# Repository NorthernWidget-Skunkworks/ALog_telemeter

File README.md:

# ALog_telemeter
ALog with a new core chip and telemetry

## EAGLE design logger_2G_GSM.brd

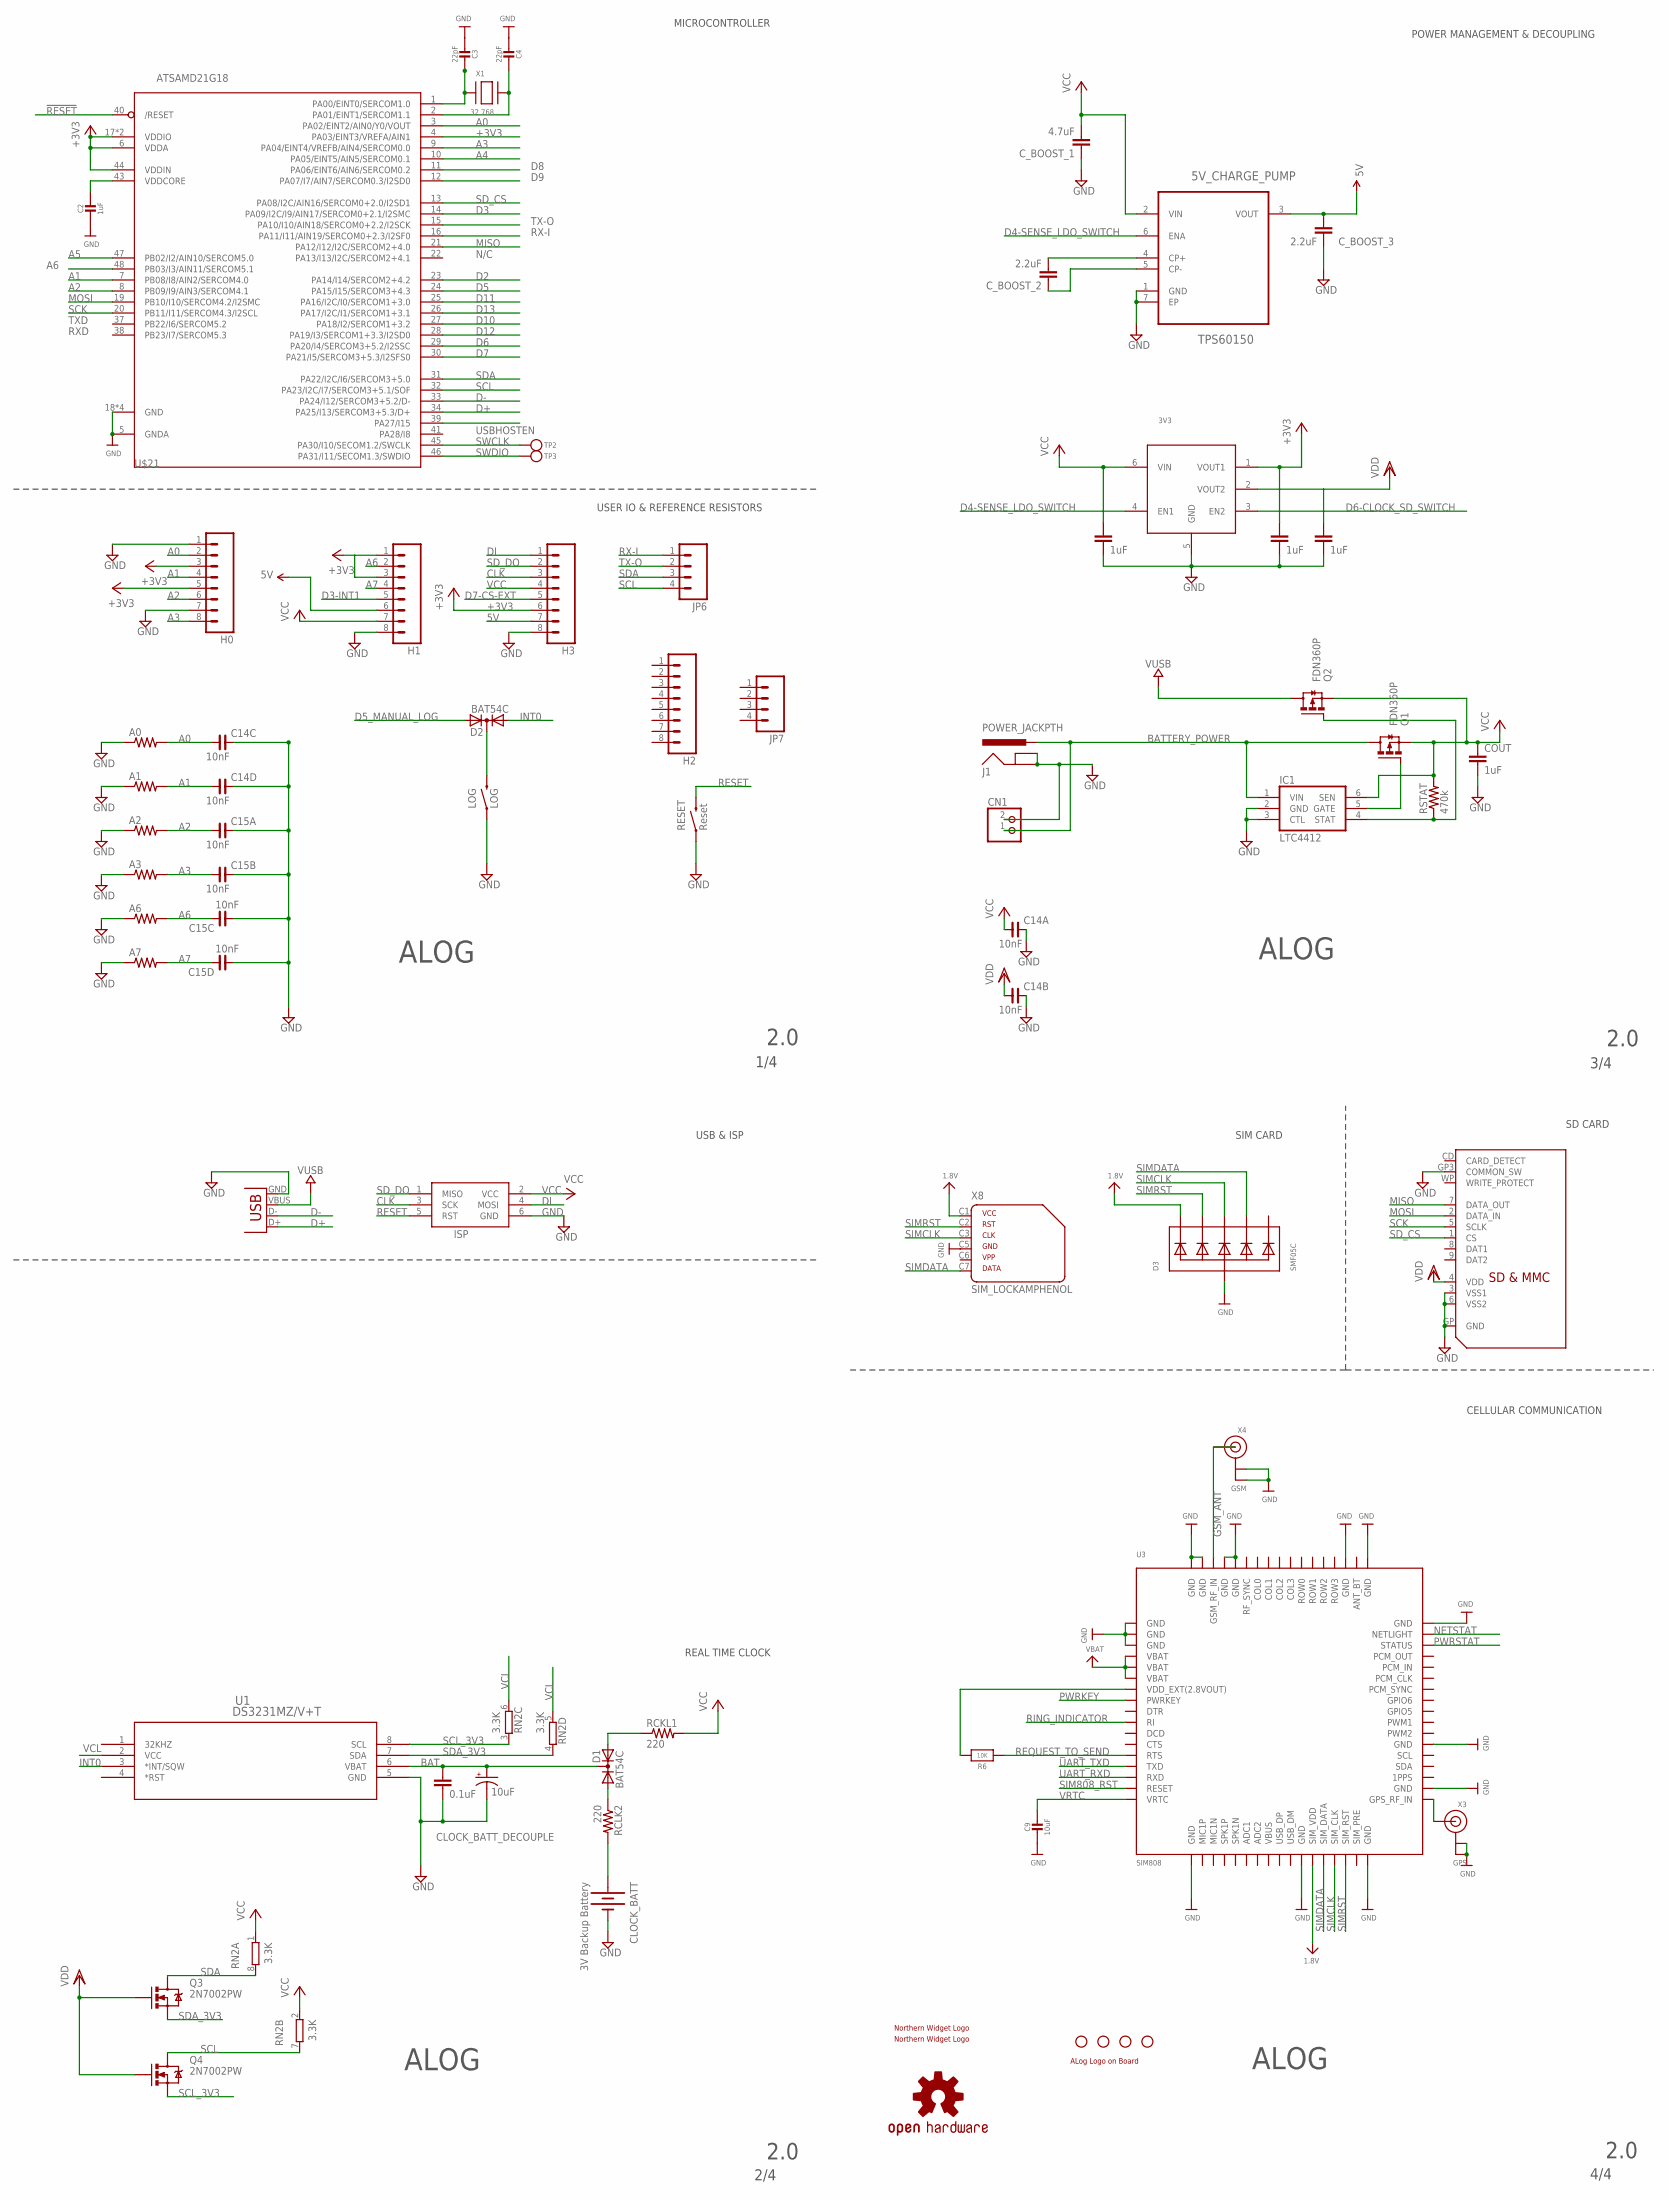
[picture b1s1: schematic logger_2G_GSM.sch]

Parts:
3V3: MIC5380; 6-TMLF
5V_CHARGE_PUMP: TPS60150; SON65P200X200X80-7N
A0, A1, A2, A3, A6, A7: R-US_0207/10; 0207/10
C2: 1uF; 0603-NO
C3, C4: 22pF; 0603-NO
C9: 10uF; 0805-NO
C14, C15: 10nF; CECJ-1206
CLOCK_BATT: 3V Backup Battery; BATTCON_12MM_PTH
CLOCK_BATT_DECOUP: 0.1uF; C0603
CLOCK_BATT_DECOUPLE: 10uF; EIA3216
CLOCK_CIN1, CLOCK_CIN2, CLOCK_CIN3: 1uF; C0603
CN1: JST_2PIN-THM; JST-PH-2-THM
COUT: 1uF; C0603
C_BOOST_1: 4.7uF; C0603
C_BOOST_2, C_BOOST_3: 2.2uF; C0603
D1, D2: BAT54C; SOT23C
D3: SMF05C; SOT363
H0, H1, H2, H3: M083.5MM-8; SCREWTERMINAL-3.5MM-8
IC1: LTC4412; TSOT23-6
ISP: AVRISP-6; AVRISP
J1: POWER_JACKPTH; POWER_JACK_PTH
JP1, JP2, JP3, JP4: STAND-OFF
JP5: USB-B; USB-B-PTH
JP6, JP7: M04SCREW; SCREWTERMINAL-3.5MM-4
LOG: LOG; TACTILE-PTH
LOGO1: OSHW-LOGOM; OSHW-LOGO-M
Q1, Q2: FDN360P; SUPER-SOT3
Q3, Q4: 2N7002PW; SOT323
R6: 10K; 0805-NO
RCKL1: 220; R0603
RCLK2: 220; R0603
RESET: Reset; TACTILE-PTH
RN2: 3.3K; 0603-ARC
RSTAT: 470k; R0603
SD: SDMMC06132; 06132
TP2, TP3: TESTPOINTROUND1.5MM; TESTPOINT_ROUND_1.5MM
U1: DS3231MZ/V+T; 21-0041B_8
U3: SIM808; SIM900_SMT
U$1: NWLOGO
U$2: ALOG_LOGO_V1_5.5MM; ALOG_LOGO_V1_SMALL
U$3: NWLOGO_MED
U$21: ATSAMD21G18; TQFN48_7MM
X1: 32.768; XTAL3215
X3: GPS; U.FL
X4: GSM; U.FL
X8: SIM_LOCKAMPHENOL; C707_10M006_512_2

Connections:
1.8V: D3.1 (C1), U3.P$29 (SIM_VDD), X8.C1 (1)
5V: 5V_CHARGE_PUMP.3 (VOUT), C_BOOST_3.2, H1.6, H3.7
!RESET: U$21.40 (/RESET)
+3V3: 3V3.1 (VOUT1), CLOCK_CIN2.1, H0.3, H0.5, H1.1, H1.3, H3.6, U$21.4 (PA03/EINT3/VREFA/AIN1), U$21.6 (VDDA), U$21.17 (VDDIO), U$21.36 (VDDIO), U$21.44 (VDDIN)
A0: A0.2, C14.C1 (1), H0.2, U$21.3 (PA02/EINT2/AIN0/Y0/VOUT)
A1: A1.2, C14.D1 (1), H0.4, U$21.7 (PB08/I8/AIN2/SERCOM4.0)
A2: A2.2, C15.A1 (1), H0.6, U$21.8 (PB09/I9/AIN3/SERCOM4.1)
A3: A3.2, C15.B1 (1), H0.8, U$21.9 (PA04/EINT4/VREFB/AIN4/SERCOM0.0)
A4: U$21.10 (PA05/EINT5/AIN5/SERCOM0.1)
A5: U$21.47 (PB02/I2/AIN10/SERCOM5.0)
A6: A6.2, C15.C2 (2), H1.2, U$21.48 (PB03/I3/AIN11/SERCOM5.1)
A7: A7.2, C15.D2 (2), H1.4
BAT: CLOCK_BATT_DECOUP.1, CLOCK_BATT_DECOUPLE.A (+), D1.3 (K), U1.6 (VBAT)
BATTERY_POWER: CN1.1 (2), IC1.1 (VIN), J1.PWR, Q1.3 (D)
CLK: H3.3, ISP.3 (SCK)
D2: U$21.23 (PA14/I14/SERCOM2+4.2)
D3: U$21.14 (PA09/I2C/I9/AIN17/SERCOM0+2.1/I2SMC)
D3-INT1: H1.5
D4-SENSE_LDO_SWITCH: 3V3.4 (EN1), 5V_CHARGE_PUMP.6 (ENA)
D5: U$21.24 (PA15/I15/SERCOM3+4.3)
D5_MANUAL_LOG: D2.2 (A2)
D6: U$21.29 (PA20/I4/SERCOM3+5.2/I2SSC)
D6-CLOCK_SD_SWITCH: 3V3.3 (EN2)
D7: U$21.30 (PA21/I5/SERCOM3+5.3/I2SFS0)
D7-CS-EXT: H3.5
D8: U$21.11 (PA06/EINT6/AIN6/SERCOM0.2)
D9: U$21.12 (PA07/I7/AIN7/SERCOM0.3/I2SD0)
D10: U$21.27 (PA18/I2/SERCOM1+3.2)
D11: U$21.25 (PA16/I2C/I0/SERCOM1+3.0)
D12: U$21.28 (PA19/I3/SERCOM1+3.3/I2SD0)
D13: U$21.26 (PA17/I2C/I1/SERCOM1+3.1)
D+: JP5.D+, U$21.34 (PA25/I13/SERCOM3+5.3/D+)
D-: JP5.D-, U$21.33 (PA24/I12/SERCOM3+5.2/D-)
DI: H3.1, ISP.4 (MOSI)
GND: 3V3.5 (GND), 5V_CHARGE_PUMP.1 (GND), 5V_CHARGE_PUMP.7 (EP), A0.1, A1.1, A2.1, A3.1, A6.1, A7.1, C2.2, C3.2, C4.2, C9.2, C14.A2 (2), C14.B2 (2), C14.C2 (2), C14.D2 (2), C15.A2 (2), C15.B2 (2), C15.C1 (1), C15.D1 (1), CLOCK_BATT.GND (-), CLOCK_BATT_DECOUP.2, CLOCK_BATT_DECOUPLE.C (-), CLOCK_CIN1.2, CLOCK_CIN2.2, CLOCK_CIN3.2, CN1.2 (1), COUT.2, C_BOOST_1.1, C_BOOST_3.1, D3.2 (A), H0.1, H0.7, H1.8, H3.8, IC1.2 (GND), IC1.3 (CTL), ISP.6 (GND), J1.GND, J1.GNDBREAK, JP5.GND, LOG.1, RESET.1, SD.3 (VSS1), SD.6 (VSS2), SD.GP (GND), SD.GP3 (COMMON_SW), U1.5 (GND), U3.P$1 (GND), U3.P$2 (GND), U3.P$3 (GND), U3.P$18 (GND), U3.P$28 (GND), U3.P$34 (GND), U3.P$36 (GND), U3.P$40 (GND), U3.P$51 (GND), U3.P$52 (GND), U3.P$54 (GND), U3.P$64 (GND), U3.P$65 (GND), U3.P$67 (GND), U3.P$68 (GND), U$21.5 (GNDA), U$21.18 (GND), U$21.35 (GND), U$21.42 (GND), U$21.THERMAL (GND), X3.1 (GND), X3.2 (GND), X4.1 (GND), X4.2 (GND), X8.C5 (4)
GSM_ANT: U3.P$66 (GSM_RF_IN), X4.3 (SIGNAL)
INT0: D2.1 (A1), U1.3 (*INT/SQW)
MISO: SD.7 (DATA_OUT), U$21.21 (PA12/I12/I2C/SERCOM2+4.0)
MOSI: SD.2 (DATA_IN), U$21.19 (PB10/I10/SERCOM4.2/I2SMC)
unnamed: D1.1 (A1), RCLK2.1
unnamed: CLOCK_BATT.VCC@1 (+), RCLK2.2
unnamed: R6.2, U3.P$7 (VDD_EXT(2.8VOUT))
unnamed: U3.P$35 (GPS_RF_IN), X3.3 (SIGNAL)
unnamed: IC1.4 (STAT), Q2.1 (G), RSTAT.1
unnamed: IC1.5 (GATE), Q1.1 (G)
unnamed: D2.3 (K), LOG.3 (2)
unnamed: 5V_CHARGE_PUMP.4 (CP+), C_BOOST_2.2
unnamed: 5V_CHARGE_PUMP.5 (CP-), C_BOOST_2.1
unnamed: C3.1, U$21.1 (PA00/EINT0/SERCOM1.0), X1.P$1
unnamed: C4.1, U$21.2 (PA01/EINT1/SERCOM1.1), X1.P$2
unnamed: D1.2 (A2), RCKL1.1
NETSTAT: U3.P$50 (NETLIGHT)
PWRKEY: U3.P$8 (PWRKEY)
PWRSTAT: U3.P$49 (STATUS)
REQUEST_TO_SEND: R6.1, U3.P$13 (RTS)
RESET: ISP.5 (RST), RESET.3 (2)
RING_INDICATOR: U3.P$10 (RI)
RX-I: JP6.1, U$21.16 (PA11/I11/AIN19/SERCOM0+2.3/I2SF0)
SCK: SD.5 (SCLK), U$21.20 (PB11/I11/SERCOM4.3/I2SCL)
SCL: JP6.4, Q4.3 (D), RN2.7 (2), U$21.32 (PA23/I2C/I7/SERCOM3+5.1/SOF)
SCL_3V3: Q4.2 (S), RN2.3 (1), U1.8 (SCL)
SDA: JP6.3, Q3.3 (D), RN2.8 (2), U$21.31 (PA22/I2C/I6/SERCOM3+5.0)
SDA_3V3: Q3.2 (S), RN2.4 (1), U1.7 (SDA)
SD_CS: SD.1 (CS), U$21.13 (PA08/I2C/AIN16/SERCOM0+2.0/I2SD1)
SD_DO: H3.2, ISP.1 (MISO)
SIM808_RST: U3.P$16 (RESET)
SIMCLK: D3.4 (C3), U3.P$31 (SIM_CLK), X8.C3 (3)
SIMDATA: D3.5 (C4), U3.P$30 (SIM_DATA), X8.C7 (6)
SIMRST: D3.3 (C2), U3.P$32 (SIM_RST), X8.C2 (2)
SWCLK: TP2.P$1, U$21.45 (PA30/I10/SECOM1.2/SWCLK)
SWDIO: TP3.P$1, U$21.46 (PA31/I11/SECOM1.3/SWDIO)
TX-O: JP6.2, U$21.15 (PA10/I10/AIN18/SERCOM0+2.2/I2SCK)
UART_RXD: U3.P$15 (RXD)
UART_TXD: U3.P$14 (TXD)
VBAT: U3.P$4 (VBAT), U3.P$5 (VBAT), U3.P$6 (VBAT)
VBUS: U3.P$25 (VBUS)
VCC: 3V3.6 (VIN), 5V_CHARGE_PUMP.2 (VIN), C14.A1 (1), CLOCK_CIN1.1, COUT.1, C_BOOST_1.2, H1.7, H3.4, IC1.6 (SEN), ISP.2 (VCC), Q1.2 (S), Q2.2 (S), RCKL1.2, RN2.1, RN2.2 (1), RSTAT.2
VCL: RN2.5 (2), RN2.6 (2), U1.2 (VCC)
VDD: 3V3.2 (VOUT2), C14.B1 (1), CLOCK_CIN3.1, Q3.1 (G), Q4.1 (G), SD.4 (VDD)
VDDCORE: C2.1, U$21.43 (VDDCORE)
VRTC: C9.1, U3.P$17 (VRTC)
VUSB: JP5.VBUS, Q2.3 (D)

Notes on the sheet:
MICROCONTROLLER
USER IO & REFERENCE RESISTORS
ALOG
USB & ISP
REAL TIME CLOCK
SD CARD
POWER MANAGEMENT & DECOUPLING
2.0
1/4
2/4
3/4
4/4
N/C
USBHOSTEN
TXD
RXD
CELLULAR COMMUNICATION
SIM CARD

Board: 2 copper layers, 67 parts (2 on the bottom side), 56 nets, no tracks yet.

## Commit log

2016-11-23 Current version of next-generation ALog
2017-01-05 some progress, keep ATAAMD21G?
2017-01-12 some progress
2018-06-17 CC-BY-SA

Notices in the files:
parts and their libraries:
SparkFun-Connectors: Licensing: CC v3.0 Share-Alike You are welcome to use this library for commercial purposes.
SparkFun-Electromechanical: Licensing: Creative Commons ShareAlike 4.0 International - https://creativecommons.org/licenses/by-sa/4.0
rc-master-smd: Copyright (C) 2007, Bob Starr
